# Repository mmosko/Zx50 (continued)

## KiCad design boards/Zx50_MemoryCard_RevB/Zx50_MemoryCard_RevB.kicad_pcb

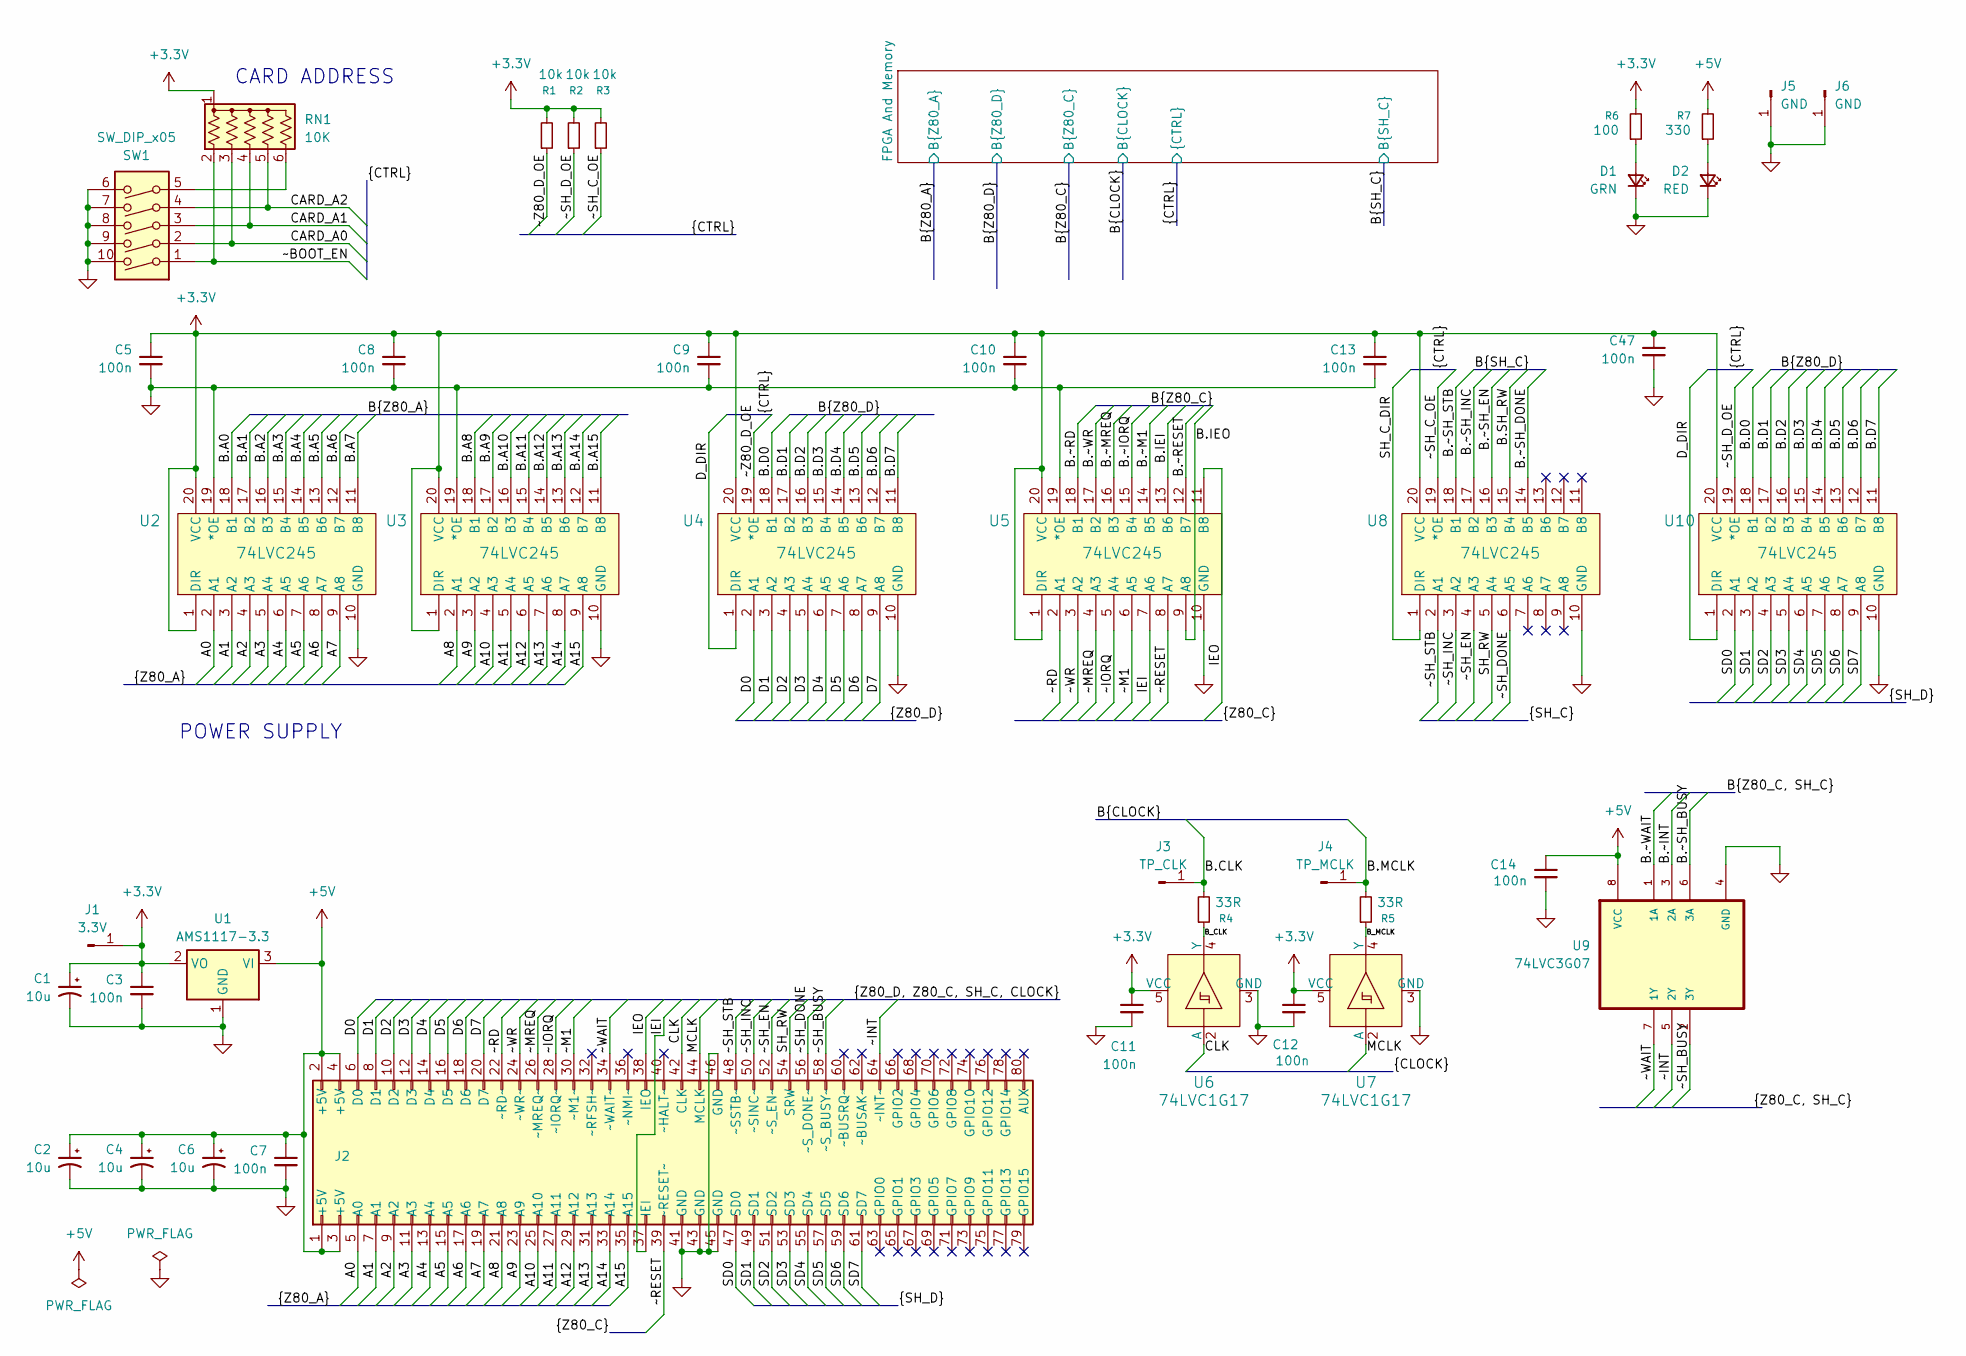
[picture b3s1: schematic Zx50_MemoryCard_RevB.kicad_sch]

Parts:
C1, C2, C4, C6: 10u; C_1206_3216Metric; MFG PN AVX TAJA106K016RNJ Tantalinium; LCSC C7171
C3, C5, C7, C8, C9, C10, C11, C12, C13, C14, C47: 100n; C_0402_1005Metric; LCSC C1525
D1: GRN; LED_0805_2012Metric; MFG_PN KT-0805G; LCSC C2297
D2: RED; LED_0805_2012Metric; MFG_PN NCD0805R1; LCSC C84256
J1: 3.3V; PinHeader_1x01_P2.54mm_Vertical
J2: Zx50_EdgeConnector; PinSocket_2x40_P2.54mm_Horizontal_Edge; DigiKey_PN 2057-PH2RA-80-UA-ND
J3: TP_CLK; PinHeader_1x01_P2.54mm_Vertical
J4: TP_MCLK; PinHeader_1x01_P2.54mm_Vertical
J5, J6: GND; PinHeader_1x01_P2.54mm_Vertical
R1, R2, R3: 10k; R_0805_2012Metric; MFG_PN 0805W8F1002T5E; LCSC C17414
R4, R5: 33R; R_0603_1608Metric; MFG_PN 0603WAF330JT5E; LCSC C23140
R6: 100; R_0805_2012Metric; MFG_PN 0805W8F1000T5E; LCSC C17408
R7: 330; R_0805_2012Metric; MFG_PN 0805W8F3300T5E; LCSC C17630
RN1: 10K; R_Array_SIP6; LCSC 4606X-AP1-103LF
SW1: SW_DIP_x05; SW_DIP_SPSTx05_Slide_9.78x14.88mm_W7.62mm_P2.54mm; LCSC 208-5
U1: AMS1117-3.3; SOT-223-3_TabPin2; Mouser_PN 926-LM1117MPX3.3NOPB
U2, U3, U4, U5, U8, U10: 74LVC245; TSSOP-20_4.4x6.5mm_P0.65mm; MFG_PART SN74LVC245APWR; LCSC C7848
U6, U7: 74LVC1G17; SOT-753; MPN SN74LVC1G17DBVR; Digi-Key_PN 296-11933-1-ND
U9: 74LVC3G07; VSSOP-8_2.3x2mm_P0.5mm; MFG_PN SN74LVC3G07DCUR; LCSC C131955

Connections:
+3.3V: C1.1, C3.1, C5.1, C8.1, C9.1, C10.1, C11.1, C12.1, C13.1, C47.1, J1.1, R1.2, R2.2, R3.2, R6.2, RN1.1 (common), U1.2 (VO), U2.1 (DIR), U2.20 (VCC), U3.1 (DIR), U3.20 (VCC), U4.20 (VCC), U5.1 (DIR), U5.20 (VCC), U6.5 (VCC), U7.5 (VCC), U8.20 (VCC), U10.20 (VCC); also elsewhere on the board
+5V: C2.1, C4.1, C6.1, C7.1, C14.1, J2.1 (+5V), J2.2 (+5V), J2.3 (+5V), J2.4 (+5V), R7.2, U1.3 (VI), U9.8 (VCC)
/A0: J2.5 (A0), U2.2 (A1)
/A1: J2.7 (A1), U2.3 (A2)
/A2: J2.9 (A2), U2.4 (A3)
/A3: J2.11 (A3), U2.5 (A4)
/A4: J2.13 (A4), U2.6 (A5)
/A5: J2.15 (A5), U2.7 (A6)
/A6: J2.17 (A6), U2.8 (A7)
/A7: J2.19 (A7), U2.9 (A8)
/A8: J2.21 (A8), U3.2 (A1)
/A9: J2.23 (A9), U3.3 (A2)
/A10: J2.25 (A10), U3.4 (A3)
/A11: J2.27 (A11), U3.5 (A4)
/A12: J2.29 (A12), U3.6 (A5)
/A13: J2.31 (A13), U3.7 (A6)
/A14: J2.33 (A14), U3.8 (A7)
/A15: J2.35 (A15), U3.9 (A8)
/B.A0: U2.18 (B1); also elsewhere on the board
/B.A1: U2.17 (B2); also elsewhere on the board
/B.A2: U2.16 (B3); also elsewhere on the board
/B.A3: U2.15 (B4); also elsewhere on the board
/B.A4: U2.14 (B5); also elsewhere on the board
/B.A5: U2.13 (B6); also elsewhere on the board
/B.A6: U2.12 (B7); also elsewhere on the board
/B.A7: U2.11 (B8); also elsewhere on the board
/B.A8: U3.18 (B1); also elsewhere on the board
/B.A9: U3.17 (B2); also elsewhere on the board
/B.A10: U3.16 (B3); also elsewhere on the board
/B.A11: U3.15 (B4); also elsewhere on the board
/B.A12: U3.14 (B5); also elsewhere on the board
/B.A13: U3.13 (B6); also elsewhere on the board
/B.A14: U3.12 (B7); also elsewhere on the board
/B.A15: U3.11 (B8); also elsewhere on the board
/B.CLK: J3.1, R4.2; also elsewhere on the board
/B.D0: U4.18 (B1), U10.18 (B1); also elsewhere on the board
/B.D1: U4.17 (B2), U10.17 (B2); also elsewhere on the board
/B.D2: U4.16 (B3), U10.16 (B3); also elsewhere on the board
/B.D3: U4.15 (B4), U10.15 (B4); also elsewhere on the board
/B.D4: U4.14 (B5), U10.14 (B5); also elsewhere on the board
/B.D5: U4.13 (B6), U10.13 (B6); also elsewhere on the board
/B.D6: U4.12 (B7), U10.12 (B7); also elsewhere on the board
/B.D7: U4.11 (B8), U10.11 (B8); also elsewhere on the board
/B.IEI: U5.13 (B6); also elsewhere on the board
/B.IEO: U5.9 (A8); also elsewhere on the board
/B.MCLK: J4.1, R5.2; also elsewhere on the board
/B.SH_RW: U8.15 (B4); also elsewhere on the board
/B.~INT: U9.3 (2A); also elsewhere on the board
/B.~IORQ: U5.15 (B4); also elsewhere on the board
/B.~M1: U5.14 (B5); also elsewhere on the board
/B.~MREQ: U5.16 (B3); also elsewhere on the board
/B.~RD: U5.18 (B1); also elsewhere on the board
/B.~RESET: U5.12 (B7); also elsewhere on the board
/B.~SH_BUSY: U9.6 (3A); also elsewhere on the board
/B.~SH_DONE: U8.14 (B5); also elsewhere on the board
/B.~SH_EN: U8.16 (B3); also elsewhere on the board
/B.~SH_INC: U8.17 (B2); also elsewhere on the board
/B.~SH_STB: U8.18 (B1); also elsewhere on the board
/B.~WAIT: U9.1 (1A); also elsewhere on the board
/B.~WR: U5.17 (B2); also elsewhere on the board
/B_CLK: R4.1, U6.4 (Y)
/B_MCLK: R5.1, U7.4 (Y)
/CARD_A0: RN1.3 (R2), SW1.2; also elsewhere on the board
/CARD_A1: RN1.4 (R3), SW1.3; also elsewhere on the board
/CARD_A2: RN1.5 (R4), SW1.4; also elsewhere on the board
/CLK: J2.42 (CLK), U6.2 (A)
/D0: J2.6 (D0), U4.2 (A1)
/D1: J2.8 (D1), U4.3 (A2)
/D2: J2.10 (D2), U4.4 (A3)
/D3: J2.12 (D3), U4.5 (A4)
/D4: J2.14 (D4), U4.6 (A5)
/D5: J2.16 (D5), U4.7 (A6)
/D6: J2.18 (D6), U4.8 (A7)
/D7: J2.20 (D7), U4.9 (A8)
/D_DIR: U4.1 (DIR), U10.1 (DIR); also elsewhere on the board
/IEI: J2.37 (IEI), U5.7 (A6)
/IEO: J2.38 (IEO), U5.11 (B8)
/MCLK: J2.44 (MCLK), U7.2 (A)
/SD0: J2.47 (SD0), U10.2 (A1)
/SD1: J2.49 (SD1), U10.3 (A2)
/SD2: J2.51 (SD2), U10.4 (A3)
/SD3: J2.53 (SD3), U10.5 (A4)
/SD4: J2.55 (SD4), U10.6 (A5)
/SD5: J2.57 (SD5), U10.7 (A6)
/SD6: J2.59 (SD6), U10.8 (A7)
/SD7: J2.61 (SD7), U10.9 (A8)
/SH_C_DIR: U8.1 (DIR); also elsewhere on the board
/SH_RW: J2.54 (SRW), U8.5 (A4)
/~BOOT_EN: RN1.2 (R1), SW1.1; also elsewhere on the board
/~INT: J2.64 (~INT~), U9.5 (2Y)
/~IORQ: J2.28 (~IORQ~), U5.5 (A4)
/~M1: J2.30 (~M1~), U5.6 (A5)
/~MREQ: J2.26 (~MREQ~), U5.4 (A3)
/~RD: J2.22 (~RD~), U5.2 (A1)
/~RESET: J2.39 (~RESET~), U5.8 (A7)
/~SH_BUSY: J2.58 (~S_BUSY~), U9.2 (3Y)
/~SH_C_OE: R3.1, U8.19 (*OE); also elsewhere on the board
/~SH_DONE: J2.56 (~S_DONE~), U8.6 (A5)
/~SH_D_OE: R2.1, U10.19 (*OE); also elsewhere on the board
/~SH_EN: J2.52 (~S_EN~), U8.4 (A3)
/~SH_INC: J2.50 (~SINC~), U8.3 (A2)
/~SH_STB: J2.48 (~SSTB~), U8.2 (A1)
/~WAIT: J2.34 (~WAIT~), U9.7 (1Y)
/~WR: J2.24 (~WR~), U5.3 (A2)
/~Z80_D_OE: R1.1, U4.19 (*OE); also elsewhere on the board
GND: C1.2, C2.2, C3.2, C4.2, C5.2, C6.2, C7.2, C8.2, C9.2, C10.2, C11.2, C12.2, C13.2, C14.2, C47.2, D1.1 (K), D2.1 (K), J2.41 (GND), J2.43 (GND), J2.45 (GND), J2.46 (GND), J5.1, J6.1, SW1.6, SW1.7, SW1.8, SW1.9, SW1.10, U1.1 (GND), U2.10 (GND), U2.19 (*OE), U3.10 (GND), U3.19 (*OE), U4.10 (GND), U5.10 (GND), U5.19 (*OE), U6.3 (GND), U7.3 (GND), U8.10 (GND), U9.4 (GND), U10.10 (GND); also elsewhere on the board
unnamed: D1.2 (A), R6.1
unnamed: D2.2 (A), R7.1
unnamed: RN1.6 (R5), SW1.5

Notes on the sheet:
CARD ADDRESS
POWER SUPPLY

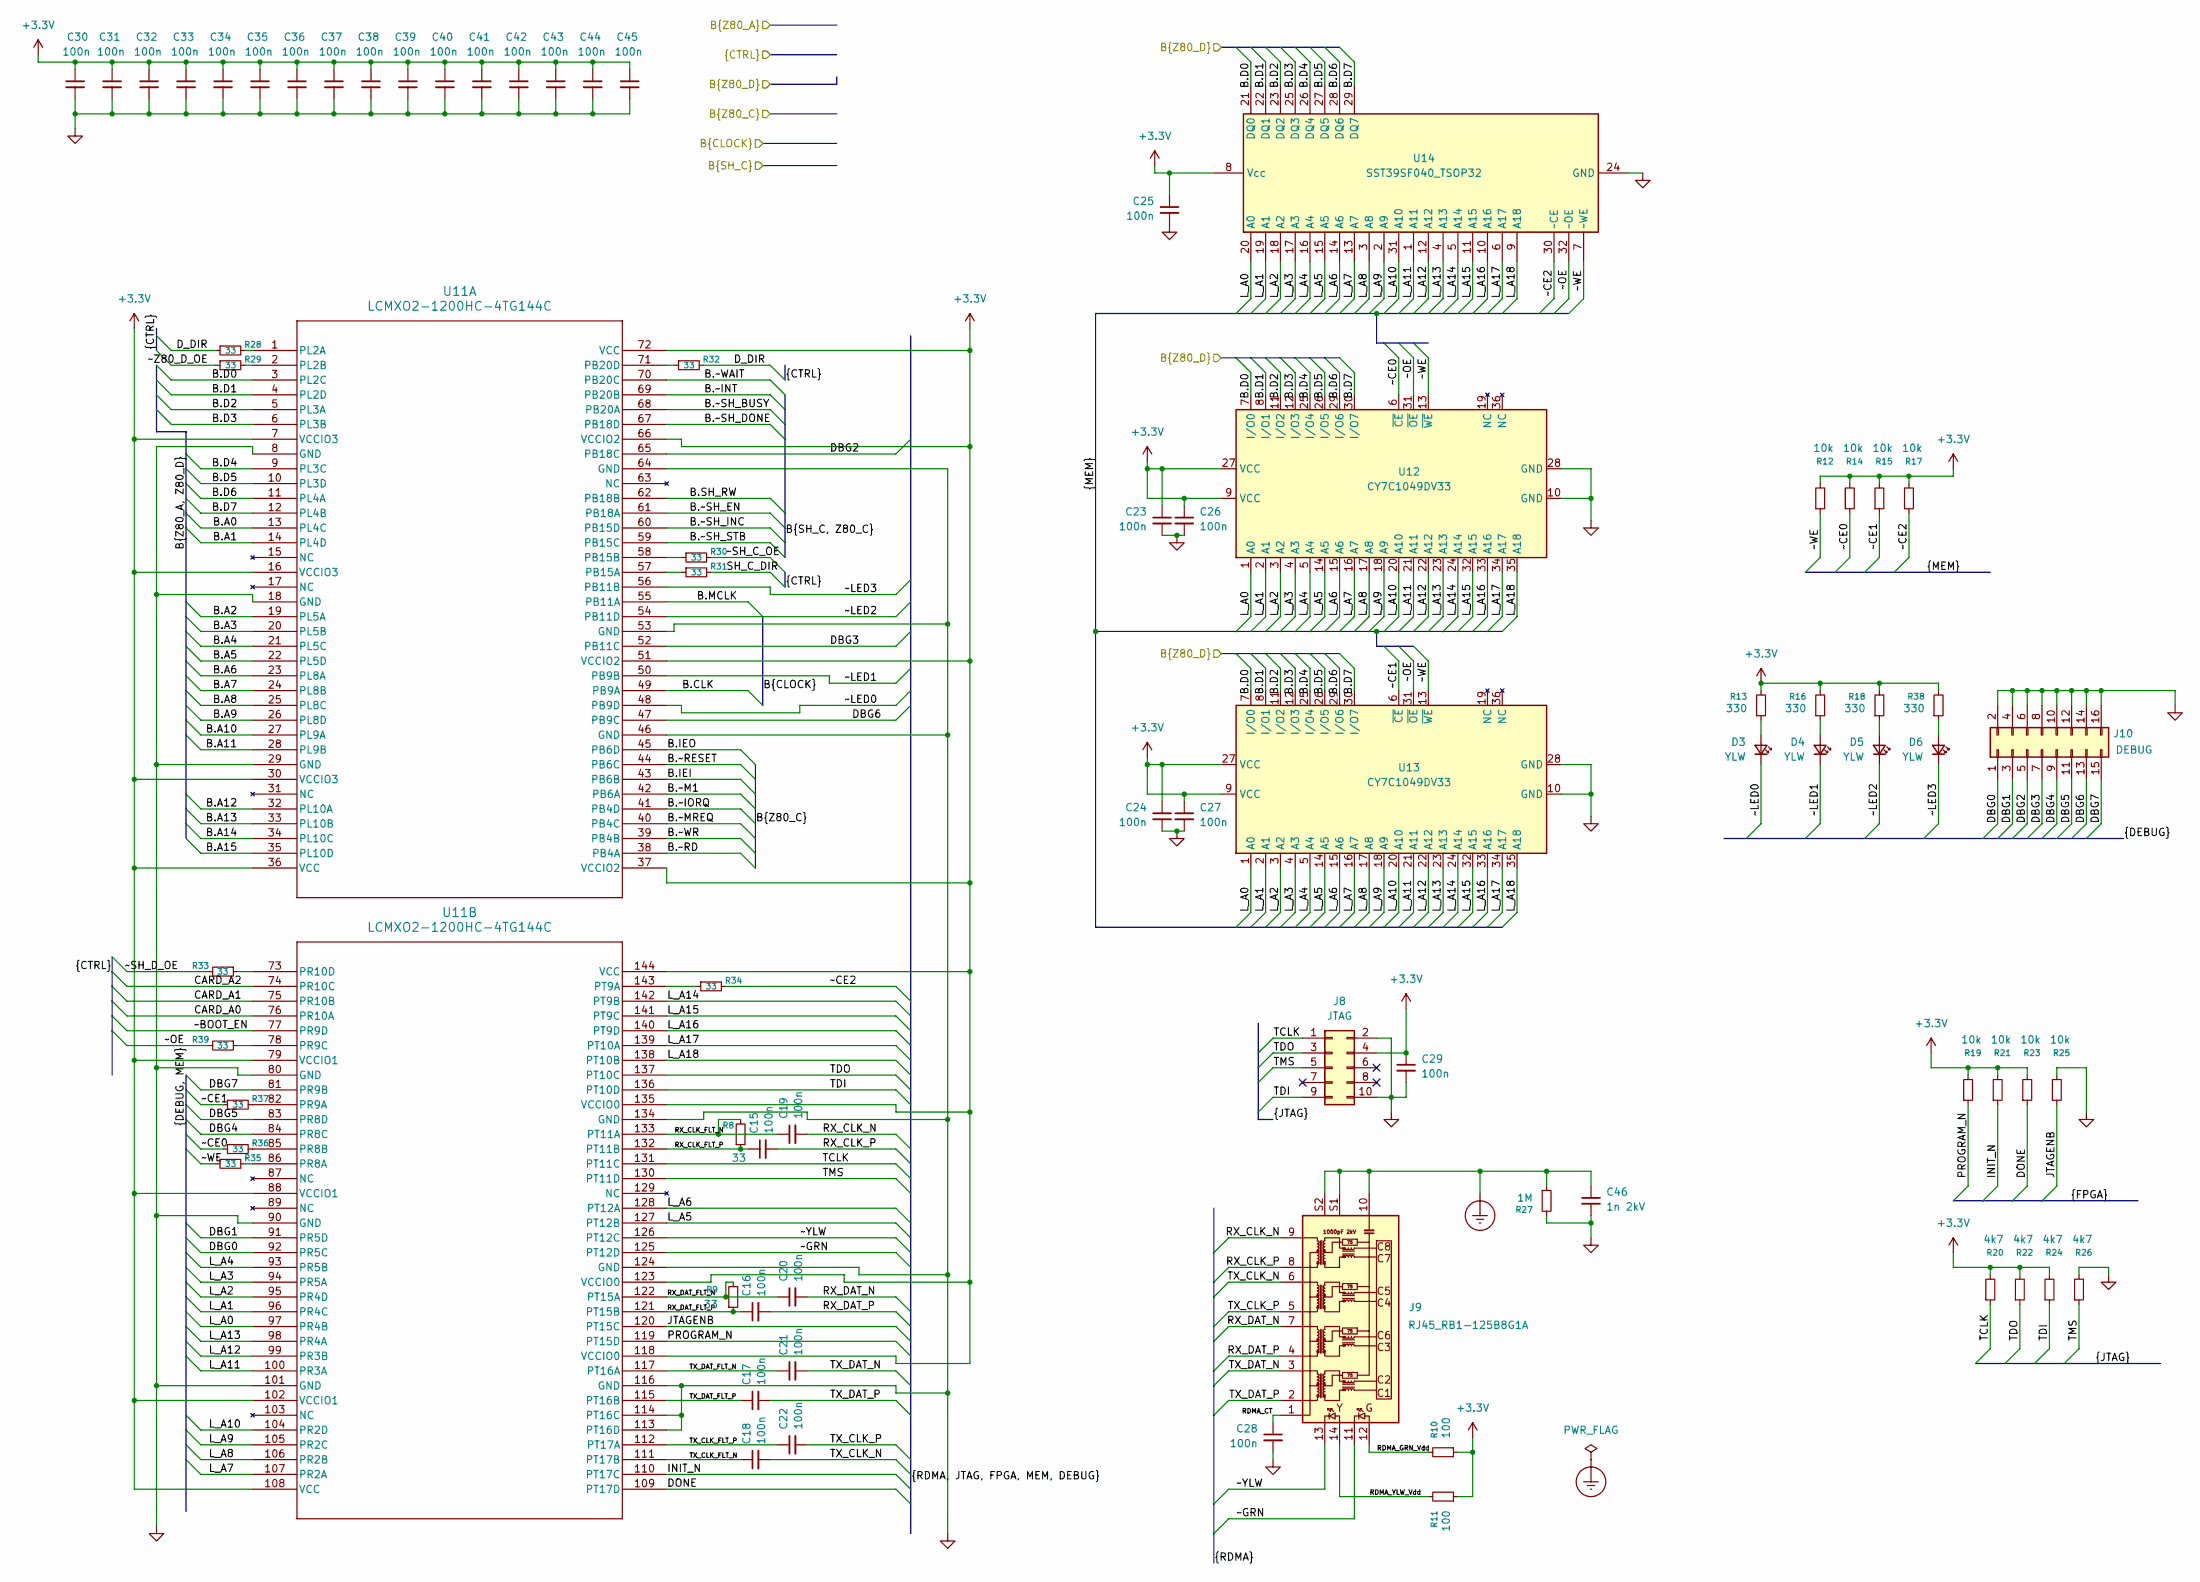
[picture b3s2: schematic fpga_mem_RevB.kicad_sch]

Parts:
C15, C16, C17, C18, C19, C20, C21, C22, C23, C24, C25, C26, C27, C28, C29, C30, C31, C32, C33, C34, C35, C36, C37, C38, C39, C40, C41, C42, C43, C44, C45: 100n; C_0402_1005Metric; LCSC C1525
C46: 1n 2kV; C_1206_3216Metric; LCSC C9196
D3, D4, D5, D6: YLW; LED_0805_2012Metric; MFG_PN KT-0805Y; LCSC C2296
J8: JTAG; IDC-Header_2x05_P2.54mm_Vertical; DigiKey_PN 732-2094-ND
J9: RJ45_RB1-125B8G1A; HANRUN_HR911130A; MFG_PN HR911130C; LCSC C50933
J10: DEBUG; IDC-Header_2x08_P2.54mm_Vertical
R8, R9, R28, R29, R30, R31, R32, R33, R34, R35, R36, R37, R39: 33; R_0402_1005Metric; MFG_PN 0402WGF1000TCE; LCSC C25076
R10, R11: 100; R_0805_2012Metric; MFG_PN 0805W8F1000T5E; LCSC C17408
R12, R14, R15, R17: 10k; R_0402_1005Metric; MFG_PN 0402W8F1002T5E; LCSC C25744
R13, R16, R18, R38: 330; R_0805_2012Metric; MFG_PN 0805W8F3300T5E; LCSC C17630
R19, R21, R23, R25: 10k; R_0402_1005Metric; MFG_PN 0402WGF1002TCE; LCSC C25744
R20, R22, R24, R26: 4k7; R_0402_1005Metric; MFG_PN 0402WGF4701TCE; LCSC C25900
R27: 1M; R_0805_2012Metric; MFG_PN 0805W8F1004T5E; LCSC C17514
U11: LCMXO2-1200HC-4TG144C; TQFP144_LAT
U12, U13: CY7C1049DV33; TSOP-II-44_10.16x18.41mm_P0.8mm; LCSC C3018881
U14: SST39SF040_TSOP32; TSOP-I-32_11.8x8mm_P0.5mm; LCSC C43651917

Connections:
+3.3V: C23.1, C24.1, C25.1, C26.1, C27.1, C29.1, C30.1, C31.1, C32.1, C33.1, C34.1, C35.1, C36.1, C37.1, C38.1, C39.1, C40.1, C41.1, C42.1, C43.1, C44.1, C45.1, J8.4, R10.1, R11.1, R12.2, R13.2, R14.2, R15.2, R16.2, R17.2, R18.2, R19.2, R20.2, R21.2, R22.2, R23.2, R24.2, R38.2, U11.7 (VCCIO3), U11.16 (VCCIO3), U11.30 (VCCIO3), U11.36 (VCC), U11.37 (VCCIO2), U11.51 (VCCIO2), U11.66 (VCCIO2), U11.72 (VCC), U11.79 (VCCIO1), U11.88 (VCCIO1), U11.102 (VCCIO1), U11.108 (VCC), U11.118 (VCCIO0), U11.123 (VCCIO0), U11.135 (VCCIO0), U11.144 (VCC), U12.9 (VCC), U12.27 (VCC), U13.9 (VCC), U13.27 (VCC), U14.8 (Vcc); also elsewhere on the board
/B.A0: U11.13 (PL4C); also elsewhere on the board
/B.A1: U11.14 (PL4D); also elsewhere on the board
/B.A2: U11.19 (PL5A); also elsewhere on the board
/B.A3: U11.20 (PL5B); also elsewhere on the board
/B.A4: U11.21 (PL5C); also elsewhere on the board
/B.A5: U11.22 (PL5D); also elsewhere on the board
/B.A6: U11.23 (PL8A); also elsewhere on the board
/B.A7: U11.24 (PL8B); also elsewhere on the board
/B.A8: U11.25 (PL8C); also elsewhere on the board
/B.A9: U11.26 (PL8D); also elsewhere on the board
/B.A10: U11.27 (PL9A); also elsewhere on the board
/B.A11: U11.28 (PL9B); also elsewhere on the board
/B.A12: U11.32 (PL10A); also elsewhere on the board
/B.A13: U11.33 (PL10B); also elsewhere on the board
/B.A14: U11.34 (PL10C); also elsewhere on the board
/B.A15: U11.35 (PL10D); also elsewhere on the board
/B.CLK: U11.49 (PB9A); also elsewhere on the board
/B.D0: U11.3 (PL2C), U12.7 (I/O0), U13.7 (I/O0), U14.21 (DQ0); also elsewhere on the board
/B.D1: U11.4 (PL2D), U12.8 (I/O1), U13.8 (I/O1), U14.22 (DQ1); also elsewhere on the board
/B.D2: U11.5 (PL3A), U12.11 (I/O2), U13.11 (I/O2), U14.23 (DQ2); also elsewhere on the board
/B.D3: U11.6 (PL3B), U12.12 (I/O3), U13.12 (I/O3), U14.25 (DQ3); also elsewhere on the board
/B.D4: U11.9 (PL3C), U12.25 (I/O4), U13.25 (I/O4), U14.26 (DQ4); also elsewhere on the board
/B.D5: U11.10 (PL3D), U12.26 (I/O5), U13.26 (I/O5), U14.27 (DQ5); also elsewhere on the board
/B.D6: U11.11 (PL4A), U12.29 (I/O6), U13.29 (I/O6), U14.28 (DQ6); also elsewhere on the board
/B.D7: U11.12 (PL4B), U12.30 (I/O7), U13.30 (I/O7), U14.29 (DQ7); also elsewhere on the board
/B.IEI: U11.43 (PB6B); also elsewhere on the board
/B.IEO: U11.45 (PB6D); also elsewhere on the board
/B.MCLK: U11.55 (PB11A); also elsewhere on the board
/B.SH_RW: U11.62 (PB18B); also elsewhere on the board
/B.~INT: U11.69 (PB20B); also elsewhere on the board
/B.~IORQ: U11.41 (PB4D); also elsewhere on the board
/B.~M1: U11.42 (PB6A); also elsewhere on the board
/B.~MREQ: U11.40 (PB4C); also elsewhere on the board
/B.~RD: U11.38 (PB4A); also elsewhere on the board
/B.~RESET: U11.44 (PB6C); also elsewhere on the board
/B.~SH_BUSY: U11.68 (PB20A); also elsewhere on the board
/B.~SH_DONE: U11.67 (PB18D); also elsewhere on the board
/B.~SH_EN: U11.61 (PB18A); also elsewhere on the board
/B.~SH_INC: U11.60 (PB15D); also elsewhere on the board
/B.~SH_STB: U11.59 (PB15C); also elsewhere on the board
/B.~WAIT: U11.70 (PB20C); also elsewhere on the board
/B.~WR: U11.39 (PB4B); also elsewhere on the board
/CARD_A0: U11.76 (PR10A); also elsewhere on the board
/CARD_A1: U11.75 (PR10B); also elsewhere on the board
/CARD_A2: U11.74 (PR10C); also elsewhere on the board
/D_DIR: R28.1, R32.2; also elsewhere on the board
/FPGA And Memory/DBG0: J10.1, U11.92 (PR5C)
/FPGA And Memory/DBG1: J10.3, U11.91 (PR5D)
/FPGA And Memory/DBG2: J10.5, U11.65 (PB18C)
/FPGA And Memory/DBG3: J10.7, U11.52 (PB11C)
/FPGA And Memory/DBG4: J10.9, U11.84 (PR8C)
/FPGA And Memory/DBG5: J10.11, U11.83 (PR8D)
/FPGA And Memory/DBG6: J10.13, U11.47 (PB9C)
/FPGA And Memory/DBG7: J10.15, U11.81 (PR9B)
/FPGA And Memory/DONE: R23.1, U11.109 (PT17D)
/FPGA And Memory/INIT_N: R21.1, U11.110 (PT17C)
/FPGA And Memory/JTAGENB: R25.1, U11.120 (PT15C)
/FPGA And Memory/L_A0: U11.97 (PR4B), U12.1 (A0), U13.1 (A0), U14.20 (A0)
/FPGA And Memory/L_A1: U11.96 (PR4C), U12.2 (A1), U13.2 (A1), U14.19 (A1)
/FPGA And Memory/L_A2: U11.95 (PR4D), U12.3 (A2), U13.3 (A2), U14.18 (A2)
/FPGA And Memory/L_A3: U11.94 (PR5A), U12.4 (A3), U13.4 (A3), U14.17 (A3)
/FPGA And Memory/L_A4: U11.93 (PR5B), U12.5 (A4), U13.5 (A4), U14.16 (A4)
/FPGA And Memory/L_A5: U11.127 (PT12B), U12.14 (A5), U13.14 (A5), U14.15 (A5)
/FPGA And Memory/L_A6: U11.128 (PT12A), U12.15 (A6), U13.15 (A6), U14.14 (A6)
/FPGA And Memory/L_A7: U11.107 (PR2A), U12.16 (A7), U13.16 (A7), U14.13 (A7)
/FPGA And Memory/L_A8: U11.106 (PR2B), U12.17 (A8), U13.17 (A8), U14.3 (A8)
/FPGA And Memory/L_A9: U11.105 (PR2C), U12.18 (A9), U13.18 (A9), U14.2 (A9)
/FPGA And Memory/L_A10: U11.104 (PR2D), U12.20 (A10), U13.20 (A10), U14.31 (A10)
/FPGA And Memory/L_A11: U11.100 (PR3A), U12.21 (A11), U13.21 (A11), U14.1 (A11)
/FPGA And Memory/L_A12: U11.99 (PR3B), U12.22 (A12), U13.22 (A12), U14.12 (A12)
/FPGA And Memory/L_A13: U11.98 (PR4A), U12.23 (A13), U13.23 (A13), U14.4 (A13)
/FPGA And Memory/L_A14: U11.142 (PT9B), U12.24 (A14), U13.24 (A14), U14.5 (A14)
/FPGA And Memory/L_A15: U11.141 (PT9C), U12.32 (A15), U13.32 (A15), U14.11 (A15)
/FPGA And Memory/L_A16: U11.140 (PT9D), U12.33 (A16), U13.33 (A16), U14.10 (A16)
/FPGA And Memory/L_A17: U11.139 (PT10A), U12.34 (A17), U13.34 (A17), U14.6 (A17)
/FPGA And Memory/L_A18: U11.138 (PT10B), U12.35 (A18), U13.35 (A18), U14.9 (A18)
/FPGA And Memory/PROGRAM_N: R19.1, U11.119 (PT15D)
/FPGA And Memory/RDMA_CT: C28.1, J9.1 (CT)
/FPGA And Memory/RDMA_GRN_Vdd: J9.12, R10.2
/FPGA And Memory/RDMA_YLW_Vdd: J9.14, R11.2
/FPGA And Memory/RX_CLK_FLT_N: C19.1, R8.2, U11.133 (PT11A)
/FPGA And Memory/RX_CLK_FLT_P: C15.1, R8.1, U11.132 (PT11B)
/FPGA And Memory/RX_CLK_N: C19.2, J9.9 (TD4-)
/FPGA And Memory/RX_CLK_P: C15.2, J9.8 (TD4+)
/FPGA And Memory/RX_DAT_FLT_N: C20.1, R9.2, U11.122 (PT15A)
/FPGA And Memory/RX_DAT_FLT_P: C16.1, R9.1, U11.121 (PT15B)
/FPGA And Memory/RX_DAT_N: C20.2, J9.7 (TD2-)
/FPGA And Memory/RX_DAT_P: C16.2, J9.4 (TD2+)
/FPGA And Memory/TCLK: J8.1, R20.1, U11.131 (PT11C)
/FPGA And Memory/TDI: J8.9, R24.1, U11.136 (PT10D)
/FPGA And Memory/TDO: J8.3, R22.1, U11.137 (PT10C)
/FPGA And Memory/TMS: J8.5, R26.1, U11.130 (PT11D)
/FPGA And Memory/TX_CLK_FLT_N: C18.1, U11.111 (PT17B)
/FPGA And Memory/TX_CLK_FLT_P: C22.1, U11.112 (PT17A)
/FPGA And Memory/TX_CLK_N: C18.2, J9.6 (TD3-)
/FPGA And Memory/TX_CLK_P: C22.2, J9.5 (TD3+)
/FPGA And Memory/TX_DAT_FLT_N: C21.1, U11.117 (PT16A)
/FPGA And Memory/TX_DAT_FLT_P: C17.1, U11.115 (PT16B)
/FPGA And Memory/TX_DAT_N: C21.2, J9.3 (TD1-)
/FPGA And Memory/TX_DAT_P: C17.2, J9.2 (TD1+)
/FPGA And Memory/~CE0: R14.1, R36.1, U12.6 (~CE)
/FPGA And Memory/~CE1: R15.1, R37.1, U13.6 (~CE)
/FPGA And Memory/~CE2: R17.1, R34.2, U14.30 (~CE)
/FPGA And Memory/~GRN: J9.11, U11.125 (PT12D)
/FPGA And Memory/~LED0: D3.1 (K), U11.48 (PB9D)
/FPGA And Memory/~LED1: D4.1 (K), U11.50 (PB9B)
/FPGA And Memory/~LED2: D5.1 (K), U11.54 (PB11D)
/FPGA And Memory/~LED3: D6.1 (K), U11.56 (PB11B)
/FPGA And Memory/~OE: R39.2, U12.31 (~OE), U13.31 (~OE), U14.32 (~OE)
/FPGA And Memory/~WE: R12.1, R35.1, U12.13 (~WE), U13.13 (~WE), U14.7 (~WE)
/FPGA And Memory/~YLW: J9.13, U11.126 (PT12C)
/SH_C_DIR: R31.2; also elsewhere on the board
/~BOOT_EN: U11.77 (PR9D); also elsewhere on the board
/~SH_C_OE: R30.2; also elsewhere on the board
/~SH_D_OE: R33.2; also elsewhere on the board
/~Z80_D_OE: R29.1; also elsewhere on the board
Earth_Protective: C46.1, J9.10 (GND), J9.S1, J9.S2, R27.1
GND: C23.2, C24.2, C25.2, C26.2, C27.2, C28.2, C29.2, C30.2, C31.2, C32.2, C33.2, C34.2, C35.2, C36.2, C37.2, C38.2, C39.2, C40.2, C41.2, C42.2, C43.2, C44.2, C45.2, C46.2, J8.2, J8.10, J10.2, J10.4, J10.6, J10.8, J10.10, J10.12, J10.14, J10.16, R25.2, R26.2, R27.2, U11.8 (GND), U11.18 (GND), U11.29 (GND), U11.46 (GND), U11.53 (GND), U11.64 (GND), U11.80 (GND), U11.90 (GND), U11.101 (GND), U11.113 (PT16D), U11.114 (PT16C), U11.116 (GND), U11.124 (GND), U11.134 (GND), U12.10 (GND), U12.28 (GND), U13.10 (GND), U13.28 (GND), U14.24 (GND); also elsewhere on the board
unnamed: D3.2 (A), R13.1
unnamed: D4.2 (A), R16.1
unnamed: D5.2 (A), R18.1
unnamed: D6.2 (A), R38.1
unnamed: R31.1, U11.57 (PB15A)
unnamed: R30.1, U11.58 (PB15B)
unnamed: R32.1, U11.71 (PB20D)
unnamed: R28.2, U11.1 (PL2A)
unnamed: R29.2, U11.2 (PL2B)
unnamed: R35.2, U11.86 (PR8A)
unnamed: R36.2, U11.85 (PR8B)
unnamed: R37.2, U11.82 (PR9A)
unnamed: R39.1, U11.78 (PR9C)
unnamed: R33.1, U11.73 (PR10D)
unnamed: R34.1, U11.143 (PT9A)

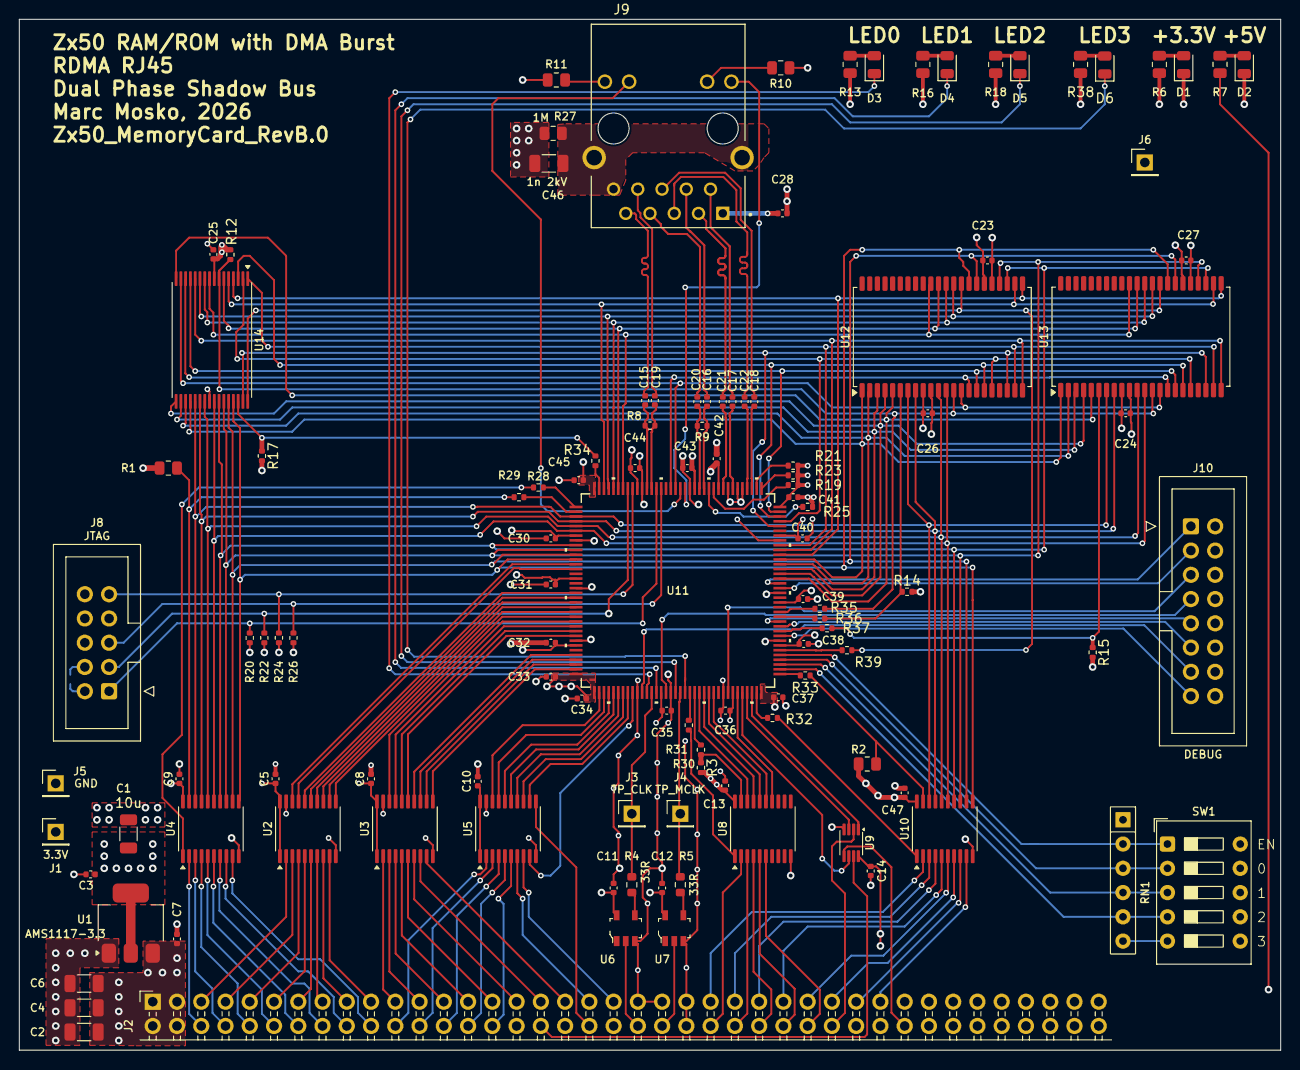
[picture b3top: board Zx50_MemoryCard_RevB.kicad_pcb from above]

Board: 4 copper layers, 132.1 x 107.9 mm, 117 parts (1 on the bottom side), 190 nets.
